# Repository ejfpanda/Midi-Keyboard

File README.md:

# Midi-Keyboard

## Overview

It has 20 keys, 2 rotary encoders, a digital-to-analog converter (I2S DAC), an sd card, LCD and uses a raspberry pi pico. You can use the rotary encoders to shift octaves and also change midi channels. The microcontroller is used to process user input into this midi keyboard.

## CAD

## PCB and schematic

## Required parts:

| Component | Amount |
| :--- | :---: |
| **Raspberry Pi Pico** | 1x |
| **MX-Style switches** | 21x |
| **1N4148 Diodes** | 20x |
| **EC11 Rotary encoder** | 2x |
| **Case** | 1x |
| **PCB** | 1x |
| **M3x25mm screws** | 4x |
| **PCM5100 I2S DAC** | 1x |
| **ST7735R** | 1x |
| **SD Card** | 1x |

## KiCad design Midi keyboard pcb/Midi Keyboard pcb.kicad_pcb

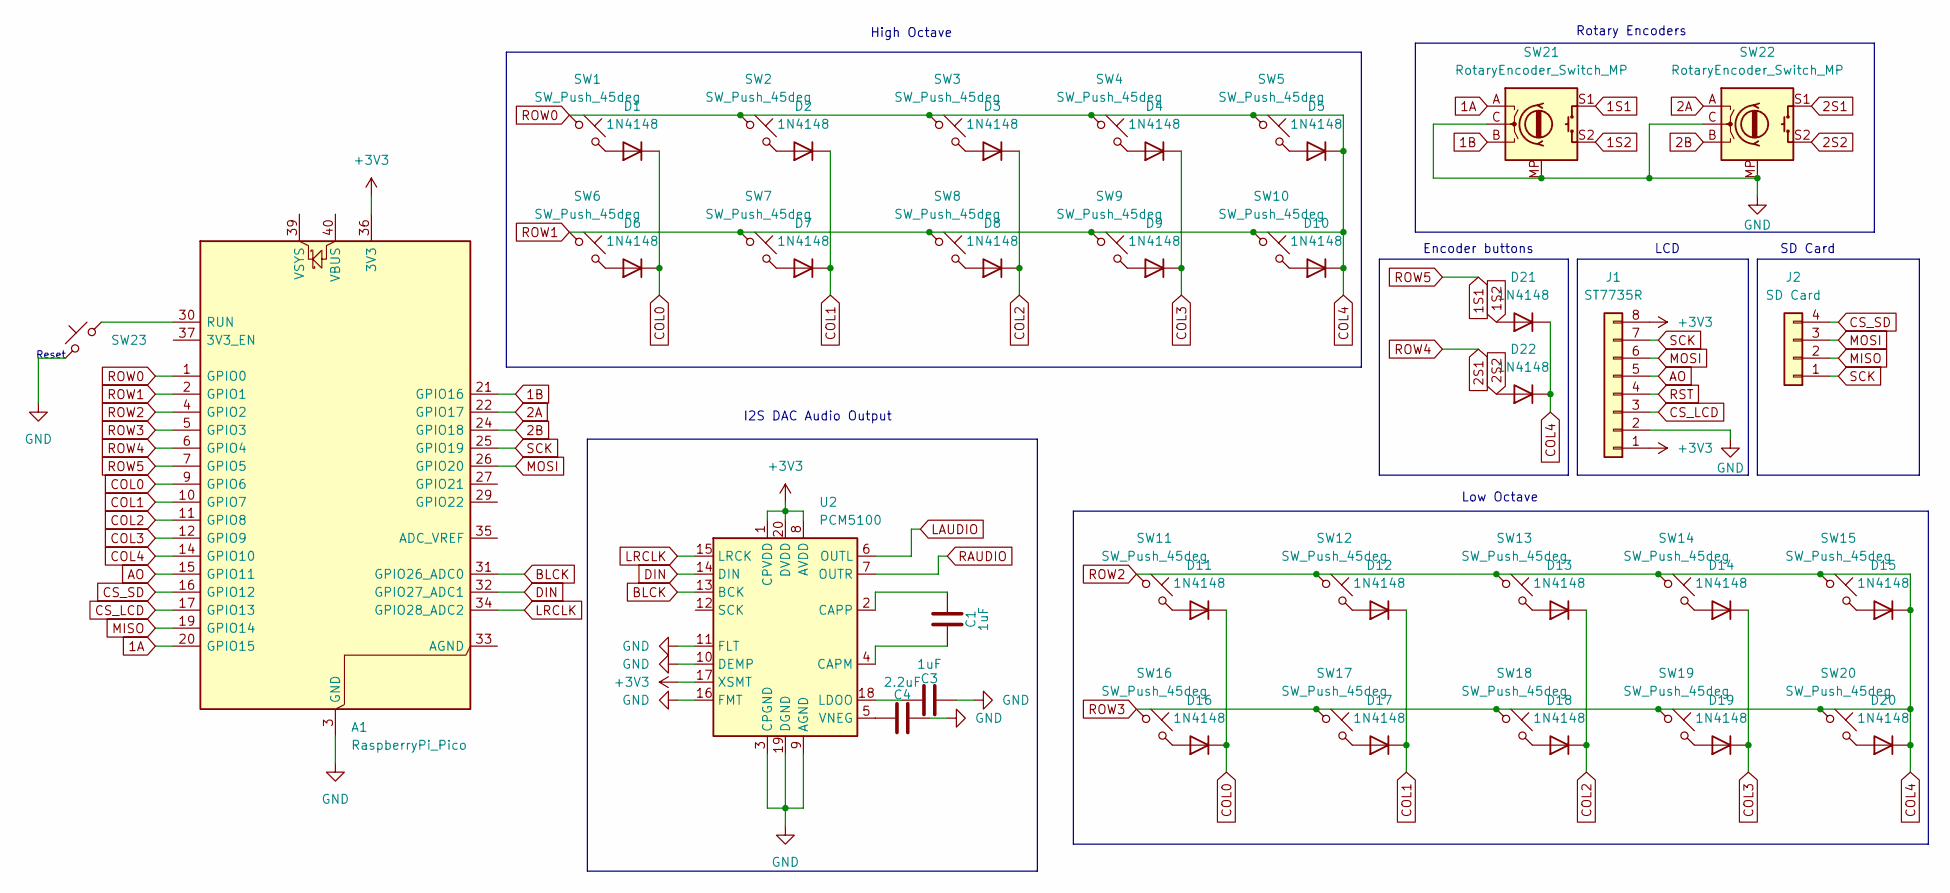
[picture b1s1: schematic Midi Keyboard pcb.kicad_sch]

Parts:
A1: RaspberryPi_Pico; RaspberryPi_Pico_Common_Unspecified
C1, C3: 1uF; CP_Axial_L10.0mm_D4.5mm_P15.00mm_Horizontal
C4: 2.2uF; CP_Axial_L10.0mm_D4.5mm_P15.00mm_Horizontal
D1, D2, D3, D4, D5, D6, D7, D8, D9, D10, D11, D12, D13, D14, D15, D16, D17, D18, D19, D20, D21, D22: 1N4148; D_DO-35_SOD27_P7.62mm_Horizontal
J1: ST7735R; PinSocket_1x08_P1.00mm_Vertical
J2: SD Card; PinSocket_1x04_P1.00mm_Vertical_SMD_Pin1Right
SW1, SW2, SW3, SW4, SW5, SW6, SW7, SW8, SW9, SW10, SW11, SW12, SW13, SW14, SW15, SW16, SW17, SW18, SW19, SW20: SW_Push_45deg; SW_Cherry_MX_1.00u_PCB
SW21, SW22: RotaryEncoder_Switch_MP; RotaryEncoder_Alps_EC11E-Switch_Vertical_H20mm
SW23: SW_Cherry_MX_1.00u_PCB
U2: PCM5100; SOP65P640X120-20N

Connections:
1A: A1.20 (GPIO15), SW21.A
1B: A1.21 (GPIO16), SW21.B
1S1: A1.7 (GPIO5), SW21.S1
1S2: D21.2 (A), SW21.S2
2A: A1.22 (GPIO17), SW22.A
2B: A1.24 (GPIO18), SW22.B
2S1: A1.6 (GPIO4), SW22.S1
2S2: D22.2 (A), SW22.S2
+3V3: A1.36 (3V3), J1.1, J1.8, U2.1 (CPVDD), U2.8 (AVDD), U2.17 (XSMT), U2.20 (DVDD)
AO: A1.15 (GPIO11), J1.5
BLCK: A1.31 (GPIO26_ADC0), U2.13 (BCK)
COL0: A1.9 (GPIO6), D1.1 (K), D6.1 (K), D11.1 (K), D16.1 (K)
COL1: A1.10 (GPIO7), D2.1 (K), D7.1 (K), D12.1 (K), D17.1 (K)
COL2: A1.11 (GPIO8), D3.1 (K), D8.1 (K), D13.1 (K), D18.1 (K)
COL3: A1.12 (GPIO9), D4.1 (K), D9.1 (K), D14.1 (K), D19.1 (K)
COL4: A1.1 (GPIO0), A1.2 (GPIO1), A1.4 (GPIO2), A1.5 (GPIO3), A1.14 (GPIO10), D5.1 (K), D10.1 (K), D15.1 (K), D20.1 (K), D21.1 (K), D22.1 (K), SW1.1, SW2.1, SW3.1, SW4.1, SW5.1, SW6.1, SW7.1, SW8.1, SW9.1, SW10.1, SW11.1, SW12.1, SW13.1, SW14.1, SW15.1, SW16.1, SW17.1, SW18.1, SW19.1, SW20.1
CS_LCD: A1.17 (GPIO13), J1.3
CS_SD: A1.16 (GPIO12), J2.4
DIN: A1.32 (GPIO27_ADC1), U2.14 (DIN)
GND: A1.3 (GND), A1.8 (GND), A1.13 (GND), A1.18 (GND), A1.23 (GND), A1.28 (GND), A1.38 (GND), C3.2, C4.2, J1.2, SW21.C, SW21.MP, SW22.C, SW22.MP, SW23.1, U2.3 (CPGND), U2.9 (AGND), U2.10 (DEMP), U2.11 (FLT), U2.16 (FMT), U2.19 (DGND)
LAUDIO: U2.6 (OUTL)
LRCLK: A1.34 (GPIO28_ADC2), U2.15 (LRCK)
MISO: A1.19 (GPIO14), J2.2
MOSI: A1.26 (GPIO20), J1.6, J2.3
unnamed: A1.30 (RUN), SW23.2
unnamed: D1.2 (A), SW1.2
unnamed: D2.2 (A), SW2.2
unnamed: D3.2 (A), SW3.2
unnamed: D4.2 (A), SW4.2
unnamed: D5.2 (A), SW5.2
unnamed: D6.2 (A), SW6.2
unnamed: D7.2 (A), SW7.2
unnamed: D8.2 (A), SW8.2
unnamed: D9.2 (A), SW9.2
unnamed: D10.2 (A), SW10.2
unnamed: D11.2 (A), SW11.2
unnamed: D12.2 (A), SW12.2
unnamed: D13.2 (A), SW13.2
unnamed: D14.2 (A), SW14.2
unnamed: D15.2 (A), SW15.2
unnamed: D16.2 (A), SW16.2
unnamed: D17.2 (A), SW17.2
unnamed: D18.2 (A), SW18.2
unnamed: D19.2 (A), SW19.2
unnamed: D20.2 (A), SW20.2
unnamed: C1.2, U2.4 (CAPM)
unnamed: C1.1, U2.2 (CAPP)
unnamed: C3.1, U2.18 (LDOO)
unnamed: C4.1, U2.5 (VNEG)
RAUDIO: U2.7 (OUTR)
RST: J1.4
SCK: A1.25 (GPIO19), J1.7, J2.1

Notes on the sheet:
SD Card
Reset
Rotary Encoders
Encoder buttons
I2S DAC Audio Output
Low Octave
High Octave
LCD

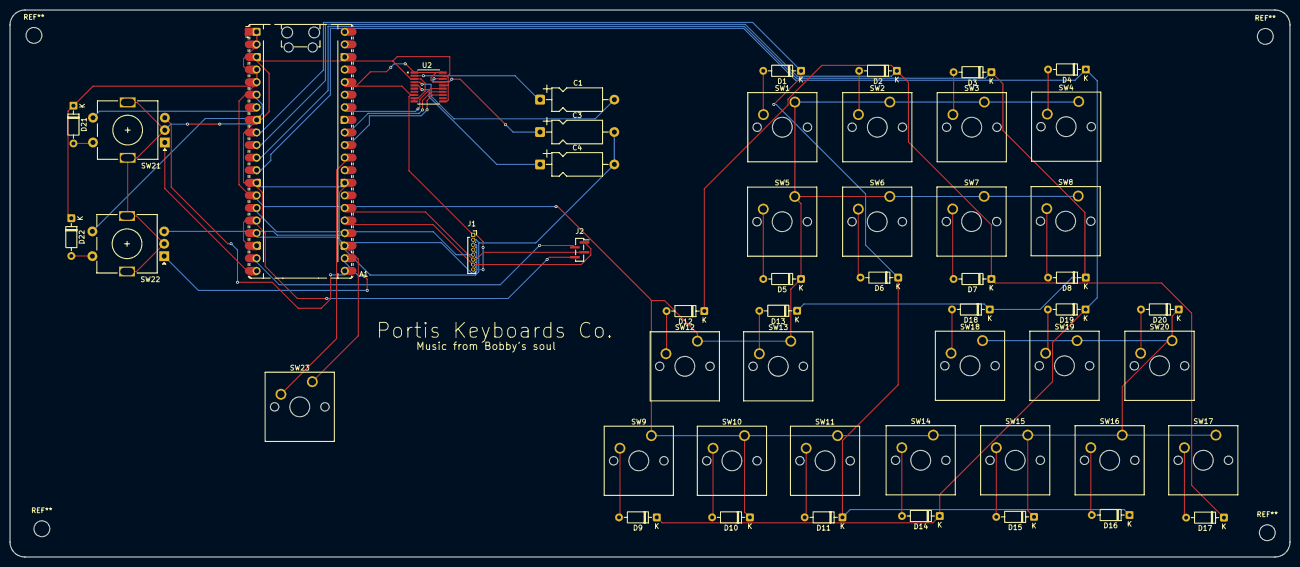
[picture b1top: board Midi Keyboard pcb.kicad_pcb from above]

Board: 2 copper layers, 258.4 x 110.4 mm, 52 parts (0 on the bottom side), 49 nets.
